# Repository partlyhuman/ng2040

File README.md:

# NG2040
### A cute DIY RP2040+2.4GHz wireless controller for Neo Geo

This is a wireless joystick and receiver for Neo Geo consoles that I designed to meet these requirments:

* Super compact joystick (6.5"x4.5" / 17x12cm)
* Super compact receiver (extends 1.5" / 4cm out from port)
* 3D printable
* Can use cheap Sanwa clones or the real thing
* No (less than 1 frame) of lag
* 2.4GHz radio, no pairing nonsense
* Long battery life with deep sleep
* USB-C rechargeable battery
* PCB using JST for tidy button wiring

It uses the ubiquitous RP2040 (specifically, the Waveshare RP2040 Tiny) and Nordic nRF24L01 radios.

## Status

The project is ready for production, but there is a compatibility issue:

The DB15 connectors used are standard depth and work perfectly with supergun setups. However, to use with Neo Geo AES consoles and their extra-deep DB15 ports, a pigtail is required. There are AES specific designs in this repository that can be built using hand-soldered pins and a 3d-printed shroud, but I was never really happy with them, so they're not part of the "official" offering here - feel free to try them out if you so desire, of course.

The joystick design continues on as a BTLE joystick, which can pair with a Neo Geo BlueRetro dongle, any other console with BlueRetro, or your PC! See my [ESP.Ra.Dio project](https://github.com/partlyhuman/esp.ra.dio).

## Build instructions

Contact me for purchasing pre-built joysticks, or a build guide will be added to the wiki shortly.

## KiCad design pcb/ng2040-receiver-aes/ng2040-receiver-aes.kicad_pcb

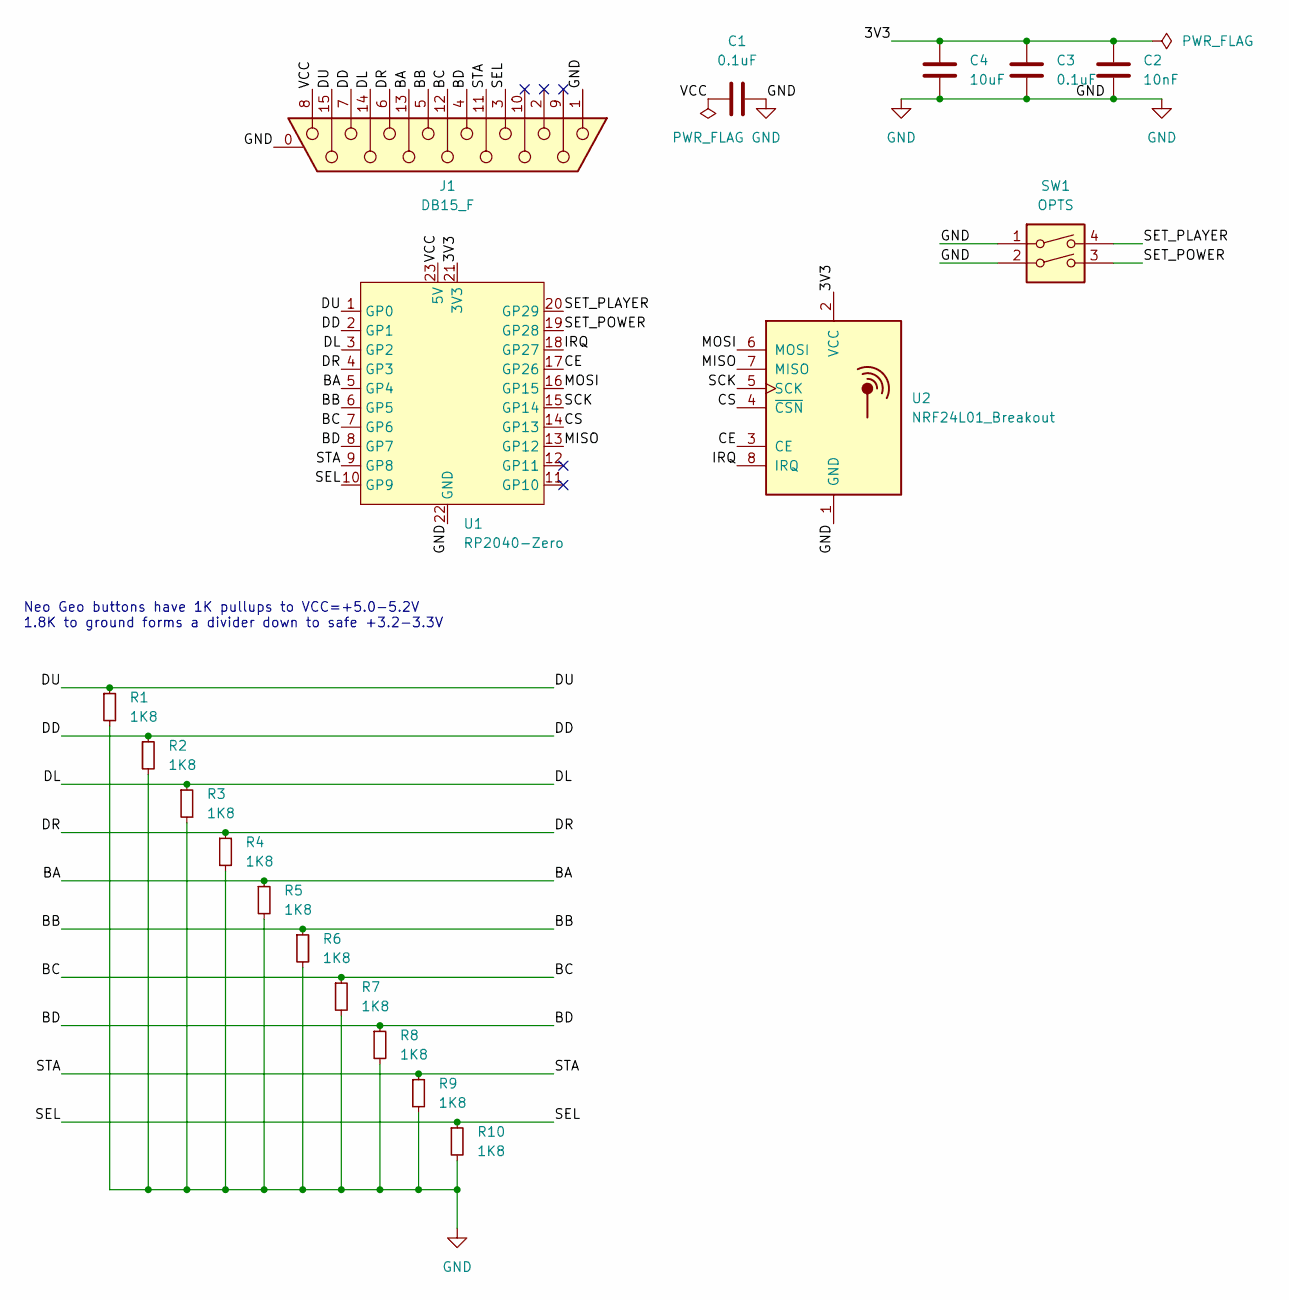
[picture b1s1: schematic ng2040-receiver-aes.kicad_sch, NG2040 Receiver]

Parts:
C1, C3: 0.1uF; C_0805_2012Metric_Pad1.18x1.45mm_HandSolder
C2: 10nF; C_0805_2012Metric_Pad1.18x1.45mm_HandSolder
C4: 10uF; C_0805_2012Metric_Pad1.18x1.45mm_HandSolder
J1: DB15_F; DIY_DB15
R1, R2, R3, R4, R5, R6, R7, R8, R9, R10: 1K8; R_0805_2012Metric_Pad1.20x1.40mm_HandSolder
SW1: OPTS; SW_DIP_SPSTx02_Slide_6.7x6.64mm_W8.61mm_P2.54mm_LowProfile
U1: RP2040-Zero
U2: NRF24L01_Breakout; NRF24L01-SMD

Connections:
/3V3: C2.1, C3.2, C4.1, U1.21 (3V3), U2.2 (VCC)
/BA: J1.13, R5.1, U1.5 (GP4)
/BB: J1.5, R6.1, U1.6 (GP5)
/BC: J1.12, R7.1, U1.7 (GP6)
/BD: J1.4, R8.1, U1.8 (GP7)
/CE: U1.17 (GP26), U2.3 (CE)
/CS: U1.14 (GP13), U2.4 (~CSN)
/DD: J1.7, R2.1, U1.2 (GP1)
/DL: J1.14, R3.1, U1.3 (GP2)
/DR: J1.6, R4.1, U1.4 (GP3)
/DU: J1.15, R1.1, U1.1 (GP0)
/IRQ: U1.18 (GP27), U2.8 (IRQ)
/MISO: U1.13 (GP12), U2.7 (MISO)
/MOSI: U1.16 (GP15), U2.6 (MOSI)
/SCK: U1.15 (GP14), U2.5 (SCK)
/SEL: J1.3, R10.1, U1.10 (GP9)
/SET_PLAYER: SW1.4, U1.20 (GP29)
/SET_POWER: SW1.3, U1.19 (GP28)
/STA: J1.11 (P111), R9.1, U1.9 (GP8)
/VCC: C1.1, J1.8, U1.23 (5V)
GND: C1.2, C2.2, C3.1, C4.2, J1.0 (PAD), J1.1, R1.2, R2.2, R3.2, R4.2, R5.2, R6.2, R7.2, R8.2, R9.2, R10.2, SW1.1, SW1.2, U1.22 (GND), U2.1 (GND)

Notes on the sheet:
Neo Geo buttons have 1K pullups to VCC=+5.0-5.2V 1.8K to ground forms a divider down to safe +3.2-3.3V

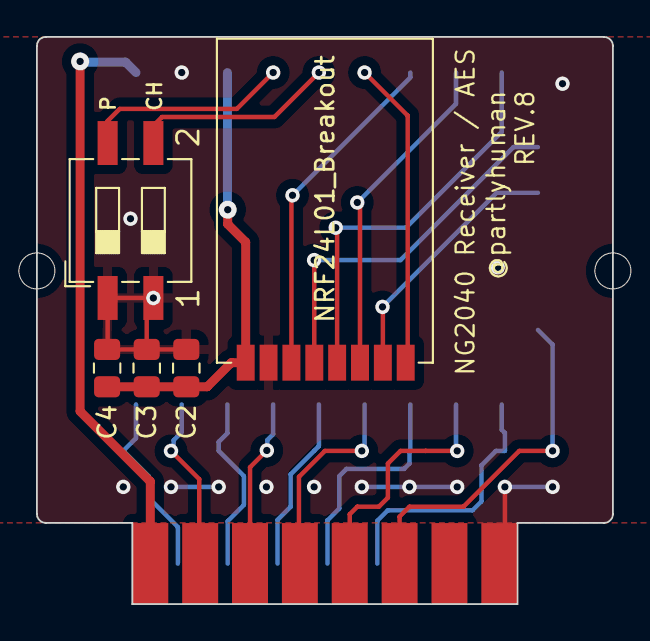
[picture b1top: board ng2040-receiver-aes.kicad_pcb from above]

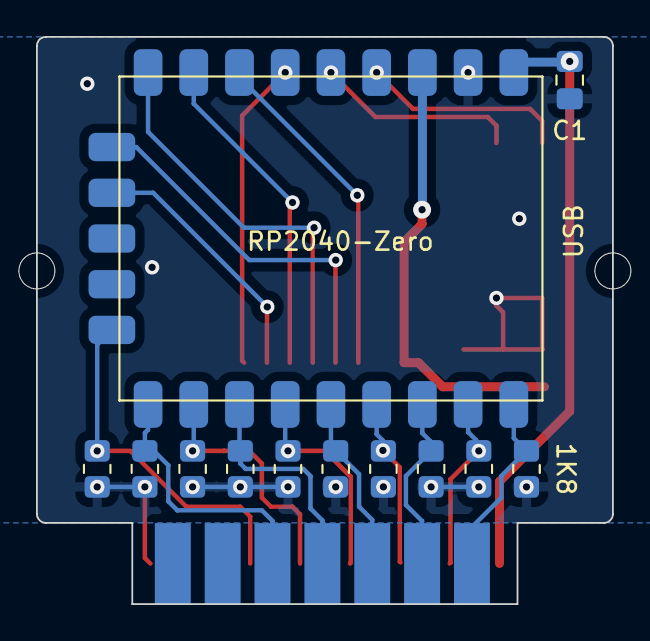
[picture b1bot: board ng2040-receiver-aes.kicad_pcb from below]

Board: 2 copper layers, 32.0 x 31.5 mm, 20 parts (12 on the bottom side), 21 nets.

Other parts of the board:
H1, H2: MountingHole_2mm

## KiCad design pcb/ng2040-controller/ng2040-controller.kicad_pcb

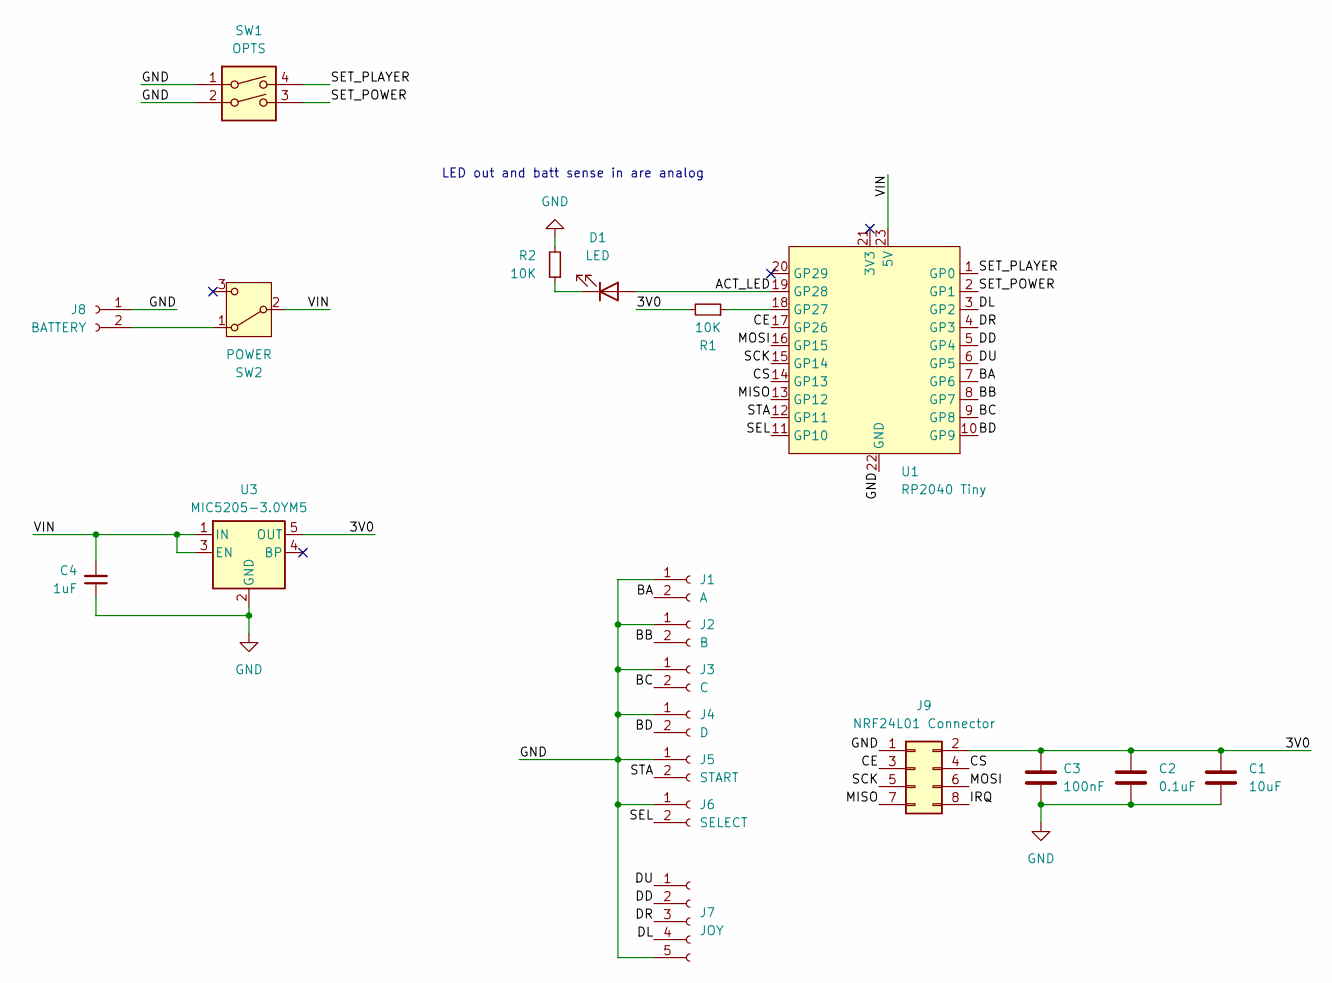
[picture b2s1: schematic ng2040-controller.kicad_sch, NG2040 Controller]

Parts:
C1: 10uF; C_0805_2012Metric_Pad1.18x1.45mm_HandSolder
C2: 0.1uF; C_0805_2012Metric_Pad1.18x1.45mm_HandSolder
C3: 100nF; C_0805_2012Metric_Pad1.18x1.45mm_HandSolder
C4: 1uF; C_0805_2012Metric_Pad1.18x1.45mm_HandSolder
D1: LED; LED_D3.0mm_Horizontal_O1.27mm_Z6.0mm
J1: A; JST_XH_B2B-XH-A_1x02_P2.50mm_Vertical
J2: B; JST_XH_B2B-XH-A_1x02_P2.50mm_Vertical
J3: C; JST_XH_B2B-XH-A_1x02_P2.50mm_Vertical
J4: D; JST_XH_B2B-XH-A_1x02_P2.50mm_Vertical
J5: START; JST_XH_B2B-XH-A_1x02_P2.50mm_Vertical
J6: SELECT; JST_XH_B2B-XH-A_1x02_P2.50mm_Vertical
J7: JOY; JST_XH_B5B-XH-A_1x05_P2.50mm_Vertical
J8: BATTERY; JST_PH_B2B-PH-K_1x02_P2.00mm_Vertical
J9: NRF24L01 Connector; PinHeader_2x04_P2.54mm_Vertical
R1, R2: 10K; R_0805_2012Metric_Pad1.20x1.40mm_HandSolder
SW1: OPTS; SW_DIP_SPSTx02_Slide_6.7x6.64mm_W8.61mm_P2.54mm_LowProfile
SW2: POWER; SW_Slide_SPDT_Angled_CK_OS102011MA1Q
U1: RP2040 Tiny; RP2040-Zero
U3: MIC5205-3.0YM5; SOT-23-5

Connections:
/3V0: C1.2, C2.2, C3.2, J9.2, R1.2, U3.5 (OUT)
/ACT_LED: D1.2 (A), U1.19 (GP28)
/BA: J1.2, U1.7 (GP6)
/BB: J2.2, U1.8 (GP7)
/BC: J3.2, U1.9 (GP8)
/BD: J4.2, U1.10 (GP9)
/CE: J9.3, U1.17 (GP26)
/CS: J9.4, U1.14 (GP13)
/DD: J7.2, U1.5 (GP4)
/DL: J7.4, U1.3 (GP2)
/DR: J7.3, U1.4 (GP3)
/DU: J7.1, U1.6 (GP5)
/IRQ: J9.8
/MISO: J9.7, U1.13 (GP12)
/MOSI: J9.6, U1.16 (GP15)
/SCK: J9.5, U1.15 (GP14)
/SEL: J6.2, U1.11 (GP10)
/SET_PLAYER: SW1.4, U1.1 (GP0)
/SET_POWER: SW1.3, U1.2 (GP1)
/STA: J5.2, U1.12 (GP11)
/VIN: C4.2, SW2.2 (B), U1.23 (5V), U3.1 (IN), U3.3 (EN)
GND: C1.1, C2.1, C3.1, C4.1, J1.1, J2.1, J3.1, J4.1, J5.1, J6.1, J7.5, J8.1, J9.1, R2.2, SW1.1, SW1.2, U1.22 (GND), U3.2 (GND)
unnamed: D1.1 (K), R2.1
unnamed: J8.2, SW2.1 (A)
unnamed: R1.1, U1.18 (GP27)

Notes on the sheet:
LED out and batt sense in are analog

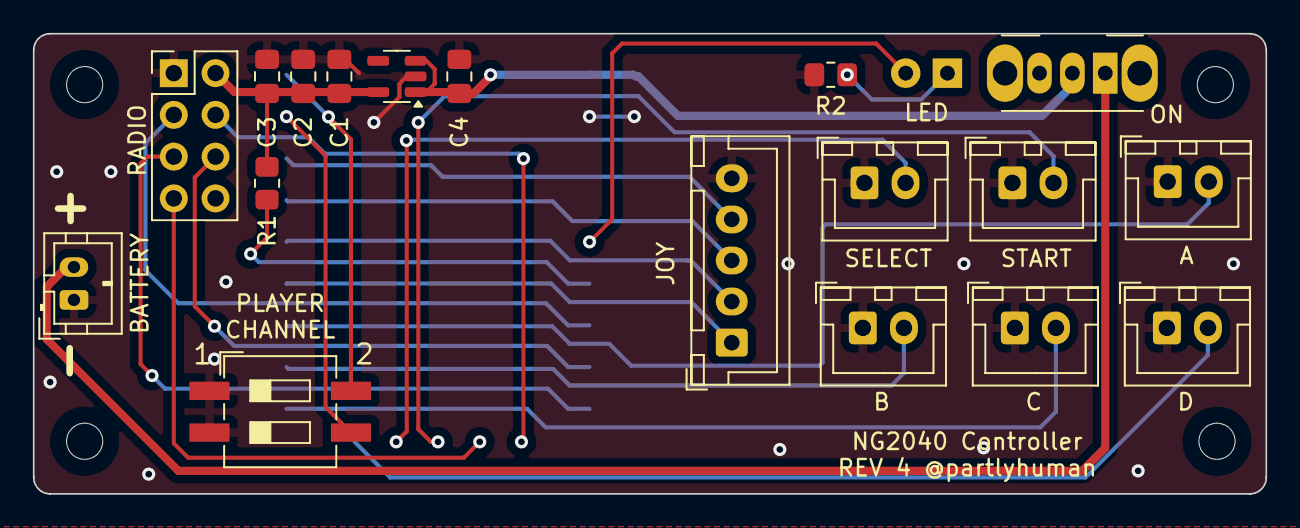
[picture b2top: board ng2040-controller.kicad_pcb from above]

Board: 2 copper layers, 75.0 x 28.0 mm, 24 parts (1 on the bottom side), 24 nets.

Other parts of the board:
H1, H2, H3, H4: MountingHole_2.2mm_M2

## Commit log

2023-11-19 Reset power level on awake
2023-11-19 Adds RP2040 joystick impl
2023-11-19 Removes non-uf2 build products
2023-11-19 Add PCB, restructure dirs
2023-11-19 PCB schematic
2023-11-19 Increases ground plane
2023-11-19 Making the right size
2023-11-19 Routing
2023-11-19 Use lowest radio power to help power supply issues
2023-11-19 Move directory
2023-11-19 Getting some unreliability around acks, changing strategy to always send. Might use more power.
2023-11-19 Correct size, add some silkscreen
2023-11-19 Adds decoupling caps
2023-11-19 Adds 3d prints
2023-11-19 Sets receiver power to min as well, stripping dead code, adding uf2
2023-11-19 Adding 3d models to pcb
2023-11-19 Adds silk
2023-11-19 Fixes errors in PCB, incorrect pin numbering on RP2040, unconnected grounds, ground mounting points, some vias to increase ground plane flood
2023-11-19 Changing receiver strategy to always send as well
2023-11-19 Arduino no sleep & P2 define
2023-11-19 Voltage dividers on button inputs for pico safety
2023-11-19 Bump up power level, add binaries
2023-11-19 Adds resistor packs for current limiting on button lines
2023-11-19 Round size up to 40mm
2023-11-19 Adds readme
2023-11-19 Add JLCJLCJLCJLC
2023-11-19 Use 0805 capacitors
2023-11-19 commit different gerber zip
2023-11-19 Rev4 wireless board with voltage dividers
2023-11-19 Fixes readme
2023-11-19 adds new print with mount points
2023-11-19 Update receiver case
2023-11-19 Updates date on PCB
2023-11-19 RGB feedback on joystick
2024-03-11 Updates documentation
2024-03-30 Kicad upgrade
2024-03-30 Rename PCB
2024-03-30 Schematic for controller board
2024-03-30 Titling schematic
2024-03-30 controller board
2024-03-30 NG2040 controller board
2024-04-01 Reworking controller board to put pico on back for LED to shine through
2024-04-19 Firmware changes for rev5
2024-05-08 Many iterations to case making it more printable without warping, refreshing gerbers, minor tweaks to firmware, adding 3d models
2024-05-12 New slim receiver case
2024-05-12 Use interrupts for every button press, move RGBLED setting off interrupt
2024-08-11 Trying various optimizations
2024-08-12 WIP moving radio to top of receiver
2024-08-12 trimming receiver board
2024-08-12 Lower bitrate / higher power?
2024-08-12 WIP changing controller into a narrower one breaking away NRF
2024-08-13 Revise controller pcb, still use RP2040 but break out to radio daughterboard pointing up
2024-09-02 Fix issues with REV2
2024-09-02 Rev3 tweaks, ext LED
2024-09-02 Modify analog sampling
2024-09-02 Remove diode as we don't want any more voltage drop
2024-09-03 WIP: Untested optimizations to controller
2024-09-03 Turn off radio while idle
2024-09-03 WIP: put LED on analog pin to modulate brightness, need to relayout
2024-09-03 Further power optimizations
2024-09-04 Rerouting
2024-09-04 Centers radio on receiver and increments to rev7
2024-09-04 Use hybrid loop-interrupt to more aggressively go into STANDBY-II
2024-09-05 Another rewrite sleeping until interrupted
2024-09-05 New battery voltage measuring method
2024-09-06 Cleanups
2024-09-06 Committing to 3V reg, rewiring to use 3V reg to indirectly measure battery
2024-09-21 Firmware revs
2024-09-22 Update 3d models, prints
2024-10-07 Minor noodling
2025-06-15 Hand-solder socket pins version of receiver variantgst
2025-06-15 AES give more padding distance to allow for plastic collar
2025-07-27 AES shave down
2025-07-27 AES removeall extra depth
